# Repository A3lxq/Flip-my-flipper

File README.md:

# Flip my flipper

> **Status: UNDER DEVELOPMENT.** This is an early-stage design project. Nothing here is built, tested, certified or ready to use. Documents are drafts and will change.

A modular, portable electronics and authorised security-research handheld, designed in India to be built from parts sold by Indian sellers. The working project name is **Synnefo Handheld**. It aims to offer Flipper-Zero-style capabilities (Sub-GHz, NFC/RFID, infrared, GPIO, Wi-Fi/BLE, USB) on an independent platform with its own firmware and an open module interface standard (SMIS), with a future Linux compute module.

This project is not affiliated with, endorsed by or connected to Flipper Devices Inc. "Flipper" and "Flipper Zero" belong to their owners.

## What is here

| File | Contents |
|---|---|
| `HANDOFF.md` | **Start here when picking the project up**: status, decisions, what was verified, gaps, how to resume, next steps |
| `01-requirements-and-architecture.md` | Requirements traceability matrix, decisions (CONFIRMED / PROPOSED / OPEN), risks |
| `02-pin-maps.md` | Pin maps for STM32H743IIT6 and STM32F429ZIT6 |
| `03-core-module.md` | Swappable MCU core-module architecture and connector table |
| `04-india-sourcing.md`, `05-deep-sourcing-and-compatibility.md` | Indian sourcing and compatibility checks (snapshots, unverified stock) |
| `06-nfc-modules.md` | Two NFC modules: PN532 and ST25R3916 |
| `07-india-regulatory.md` | Indian regulatory research (not legal advice) |
| `08-smis-v0.2.md` | Synnefo Module Interface Standard v0.2 |
| `09-power-architecture.md` | Power architecture v1 |
| `10-firmware-architecture.md` | Firmware architecture v0.1 and RTOS decision record |
| `11-os-options-and-linux-architecture.md` | Other OS options and the Linux-first (Flipper One-style) question |
| `hardware/pinouts/` | Module pinout tables (with how well each pinout is known) and the connection diagrams (system and SM-S port) |
| `hardware/kicad/` | KiCad skeletons for the PN532 adapter and the ST25R3916 module, with ERC/DRC outputs |
| `firmware/board/` | Generated pin headers for both MCUs |
| `firmware/zephyr/` | Zephyr 4.5.0 toolchain setup and the three build-level de-risk test apps with results |
| `sourcing/quote-requests.md` | Drafts of quote and stock-confirmation requests to Indian sellers (not sent) |
| `research/` | Condensed research-agent reports behind the documents (limits listed in its README) |
| `CONTRIBUTING.md` | How to contribute and what the licence requires |
| `CHAT_SUMMARY.md` | Project log: decisions, findings, corrections, open items |
| `tools/` | Scripts that solve and check the pin maps |

## Ground rules

- **Lawful use only.** The device is meant for authorised testing, electronics development and education. It must not include jamming or blocking functions, and transmit features are designed to stay inside licence-exempt bands and power limits.
- **Not legal advice.** The regulatory notes list what sources say, with their gaps. They have not been reviewed by a lawyer or a test lab. Check the rules in your country before building or selling anything.
- **Stock, prices and datasheet figures are snapshots** found during research and may be wrong or out of date. Verify against the manufacturer's current datasheet and the seller before relying on anything.
- **Safety:** this design involves lithium cells and RF circuits. Do not build it without the knowledge and equipment to do so safely.

## License

GNU General Public License v3.0 or later, the same family of licence used by the Flipper Zero firmware. See [LICENSE](LICENSE), [NOTICE](NOTICE) and [CONTRIBUTING.md](CONTRIBUTING.md).

In short: anyone may use the source and build from it; if they distribute a modified version, they must publish their source under the GPL too. We ask that improvements be contributed back through pull requests, but the licence itself cannot require that.

Earlier commits (the first two) were published under Apache-2.0; anyone who copied that version keeps those rights for that version.

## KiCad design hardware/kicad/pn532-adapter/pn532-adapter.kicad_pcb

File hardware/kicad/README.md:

# KiCad skeletons for the two NFC modules

Status: **skeleton v0.1 (2026-11-02)**. Not fabricable. Nothing has been routed, ordered or built.

| Project | What it is | State |
|---|---|---|
| `pn532-adapter/` | SM-S adapter carrying the PN532 V3 breakout (Variant A, `06-nfc-modules.md` §3) | schematic + placement-only PCB (unrouted) |
| `st25r3916-module/` | ST25R3916 module (Variant B, `06-nfc-modules.md` §5) | **block-level schematic only** (blocked on ST documents and chip sourcing); no PCB |
| `lib/` | shared symbols (`synnefo.kicad_sym`) and footprints (`synnefo.pretty/`) | generic geometry, to check per chosen part |
| `tools/gen_kicad.py` | generator for all of the above (Python standard library) | reproducible: `python3 tools/gen_kicad.py hardware/kicad` |
| `checks/` | KiCad ERC, DRC and netlist outputs from this run | see below |

Open the `.kicad_pro` files with KiCad 8 or newer. The files were generated in the KiCad 8 file format and checked with `kicad-cli` 10.0.8 (official `kicad/kicad:10.0` container). Edit the generator (not the generated files) if you want the changes to survive a regeneration.

## What was checked

- **PN532 adapter schematic:** KiCad ERC reports 0 violations. The exported netlist has exactly the intended connections (`checks/pn532-adapter.nets.txt`): the SMIS SM-S port pins go to SCK, MOSI, MISO, CS (= the breakout's SSEL), IRQ; IDC and IDD go to the ID EEPROM; 3V3_P feeds the EEPROM and, through jumper JP1, the breakout; RSTPDN is pulled up.
- **PN532 adapter PCB:** KiCad DRC reports **no clearance, courtyard or board-edge violations**; the 23 "unconnected items" are the unrouted nets (expected for a placement-only board). Rendered and inspected visually.
- **ST25R3916 schematic:** KiCad ERC reports 4 errors, all intentional open items on the placeholder block: the crystal pins `XTI`, `XTO` and the antenna pin are unconnected (`checks/st25r3916-module.erc.rpt`).
- **Not checked:** electrical correctness of any value against datasheets, footprint geometry against real parts, signal integrity, EMC, or anything on the real breakout board.

## Unverified items (must be resolved before fabrication)

PN532 adapter:
1. **PN532 V3 breakout header pin order and position.** Signal names come from the Elechouse guide; the physical order, pitch and which of the board's two headers (J1 10-pin, J2 8-pin in the vendor schematic) carry which signal were not verified. Buy the board, measure it, and fix symbol `PN532_V3_Header_UNVERIFIED_ORDER`, the footprint and the placement.
2. **Breakout supply and I/O levels.** The board's regulator and the PVDD source were not found; the adapter powers it from 3V3_P through JP1 (default 1-2). Do not use 5V_P until measured (`06-nfc-modules.md` §4.2). DIP switch settings (SPI) are on the breakout, not the adapter; verify with a meter.
3. **ID EEPROM.** 24C02-class SOIC-8, address 0x50. ElectronicsComp stocks the M24C04-WMN6P (SOIC-8) and a DIP-8 24C02; the M24C04's pin 1 is not a plain A0, so check its datasheet before freezing. WP is grounded (programmable); decide the production setting.
4. **Connector.** The footprint is a generic 2x05 2.54 mm vertical header with IDC pin numbering; the real part (Probots 10-pin right-angle shrouded box header was found in stock), its orientation, outline and mating cable are not chosen.
5. **Passives.** 0603 pad geometry is approximate; the 10 uF value and voltage rating are not selected; IRQ pull-up, if any, belongs on the carrier (SMIS) and is not on the adapter.
6. **Routing, mounting holes, board shape, silkscreen.** Not done.

ST25R3916 module:
1. Pin numbers marked `TBD-n` are unknown; only pins 1, 3, 7, 8, 9, 10, 11, 14 and 33 come from DS12484 Rev 3 text (an old revision).
2. The decoupling capacitor net assignments, the VDD_RF/VDD_DR tie and the supply plan are placeholders to confirm against DS12484/DS13541 Figure 1 and §4.2.11.
3. Absent on purpose: antenna coil, EMC filter, matching network, 27.12 MHz crystal and load capacitors, exposed-pad thermal vias, layout. They need AN5276, AN5240, AN5322, AN5592 and the NFC08A1 design files (`06-nfc-modules.md` §9).
4. No Indian source for the chip was found (`04-` to `06-`).

## Parts list (draft, nothing ordered; Indian-stock status from `04-`, `05-`, `06-`)

PN532 adapter:

| Ref | Part | Source and status |
|---|---|---|
| (module) | PN532 V3 breakout | DNA Tech India, ₹317.43 incl. GST, stock 50 (page opened 2026-11-01) |
| J1 | 2x05 2.54 mm shrouded box header | Probots, ₹17 incl. GST, in stock (right-angle); orientation/footprint to confirm |
| JP1, J2 | 1x03 and 1x08 2.54 mm pin headers, shunt | generic; not yet searched |
| U1 | 24C02-class EEPROM, SOIC-8 | ElectronicsComp M24C04-WMN6P ₹17 ex GST (154 in stock); check pin-1 difference |
| C1 | 100 nF 0603 | generic stocked family (Evelta, Probots listings); part not chosen |
| C2 | 10 uF 0603, rating TBD | Probots has a Samsung 22 uF 0805; 0603 10 uF not chosen |
| R1 | 10 kohm 0603 | generic stocked family |

ST25R3916 module: chip, crystal, antenna parts all TBD (see unverified list); ID EEPROM and decoupling as for the adapter.

## Reproduce the checks

```bash
cd hardware/kicad
k() { docker run --rm --user "$(id -u):$(id -g)" -e HOME=/tmp -v "$PWD:/work" -w /work kicad/kicad:10.0 kicad-cli "$@"; }
k sch erc --severity-all --format report -o /work/checks/pn532-adapter.erc.rpt pn532-adapter/pn532-adapter.kicad_sch
k pcb drc --severity-all --format report -o /work/checks/pn532-adapter.drc.rpt pn532-adapter/pn532-adapter.kicad_pcb
```

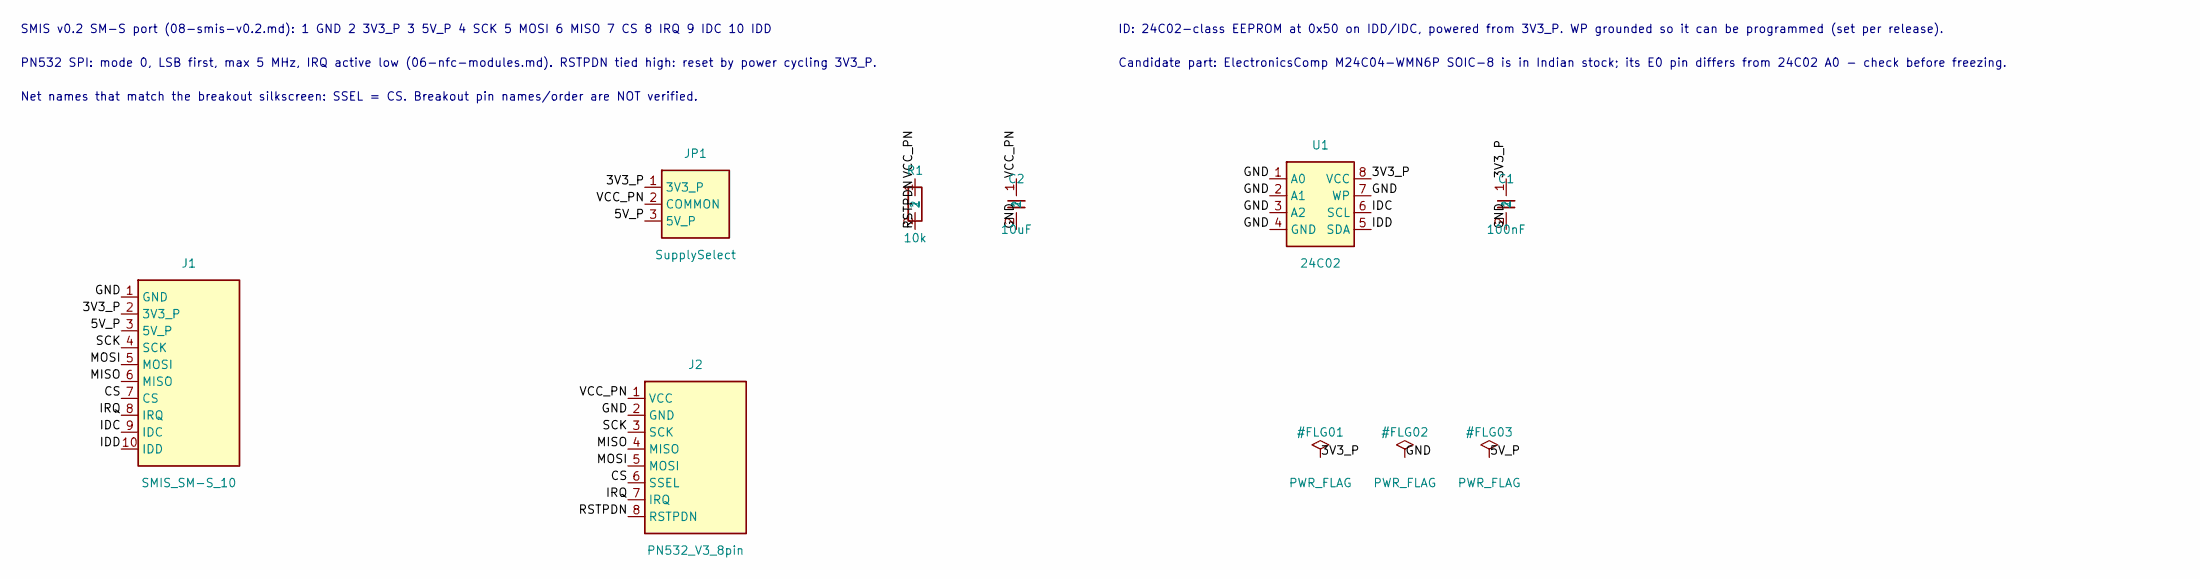
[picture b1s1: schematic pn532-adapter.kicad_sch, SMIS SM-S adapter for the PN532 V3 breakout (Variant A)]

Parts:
C1: 100nF; C_0603_1608Metric
C2: 10uF; C_0603_1608Metric
J1: SMIS_SM-S_10; IDC_Header_2x05_P2.54mm_Vertical
J2: PN532_V3_8pin; PinHeader_1x08_P2.54mm_Vertical
JP1: SupplySelect; PinHeader_1x03_P2.54mm_Vertical
R1: 10k; R_0603_1608Metric
U1: 24C02; SOIC-8_3.9x4.9mm_P1.27mm

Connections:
3V3_P: C1.1, J1.2 (3V3_P), JP1.1 (3V3_P), U1.8 (VCC)
5V_P: J1.3 (5V_P), JP1.3 (5V_P)
CS: J1.7 (CS), J2.6 (SSEL)
GND: C1.2, C2.2, J1.1 (GND), J2.2 (GND), U1.1 (A0), U1.2 (A1), U1.3 (A2), U1.4 (GND), U1.7 (WP)
IDC: J1.9 (IDC), U1.6 (SCL)
IDD: J1.10 (IDD), U1.5 (SDA)
IRQ: J1.8 (IRQ), J2.7 (IRQ)
MISO: J1.6 (MISO), J2.4 (MISO)
MOSI: J1.5 (MOSI), J2.5 (MOSI)
RSTPDN: J2.8 (RSTPDN), R1.2
SCK: J1.4 (SCK), J2.3 (SCK)
VCC_PN: C2.1, J2.1 (VCC), JP1.2 (COMMON), R1.1

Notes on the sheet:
SMIS v0.2 SM-S port (08-smis-v0.2.md): 1 GND 2 3V3_P 3 5V_P 4 SCK 5 MOSI 6 MISO 7 CS 8 IRQ 9 IDC 10 IDD
PN532 SPI: mode 0, LSB first, max 5 MHz, IRQ active low (06-nfc-modules.md). RSTPDN tied high: reset by power cycling 3V3_P.
Net names that match the breakout silkscreen: SSEL = CS. Breakout pin names/order are NOT verified.
ID: 24C02-class EEPROM at 0x50 on IDD/IDC, powered from 3V3_P. WP grounded so it can be programmed (set per release).
Candidate part: ElectronicsComp M24C04-WMN6P SOIC-8 is in Indian stock; its E0 pin differs from 24C02 A0 - check before freezing.

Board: 2 copper layers, 7 parts (0 on the bottom side), 12 nets, no tracks yet.

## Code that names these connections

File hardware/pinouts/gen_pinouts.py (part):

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

def port_pins(chip_map, n):
    s = f"IDD {pin(chip_map, f'IDD_P{n}')} IDC {pin(chip_map, f'IDC_P{n}')} IRQ {pin(chip_map, f'IRQ_P{n}')}"
    if n <= 5:
        s += f" CS {pin(chip_map, f'CS_P{n}')}"
    return s
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}
MOD_NOTE = {
    "CC1101 module (chip pins)": "GDO2 (pin 3 [P]) has no contact; vendor breakout headers differ (8 and 10 pin boards)",
    "PN532 V3 breakout (signals)": "header ORDER unverified [V]; RSTPDN pulled up on the adapter; chip pins [P]: NSS 27, MOSI 28, MISO 29, SCK 30, IRQ 25, RSTPD_N 38",
    "ST25R3916 module (chip pins)": "I2C_EN tied to GND; no reset pin; other pin numbers unknown until DS12484 Table 2 is read",
}

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    ax.set_ylim(0, 17)
    ax.axis("off")
    ax.text(12, 16.65, "SM-S port: contact-by-contact connection of the SPI modules (port P1 shown)", ha="center", fontsize=15, fontweight="bold")
    ax.text(12, 16.3, "Left: MCU pins (F429 | H743). Centre: SMIS v0.2 contacts (2x5 header, IDC numbering). Right: module pins. "
            "Tags: [P] datasheet read, [V] vendor guide, [K] my recollection, unverified, ? unknown.", ha="center", fontsize=9, color="#444")
    row_h = 0.62
    top = 15.2
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    py = 6.9
    ax.text(0.4, py, "SM-U port (P8, UART) with RDM6300 125 kHz reader", fontsize=11.5, fontweight="bold")
    ax.text(0.4, py - 0.35, "contacts 4-8 change meaning per class; 1, 2, 3, 9, 10 never change", fontsize=8.6, color="#444")
    SMU = ["GND", "3V3_P", "5V_P", "TX (module out)", "RX (module in)", "IRQ", "GPIO", "n/c", "IDC", "IDD"]
    SMU_MCU = {"TX (module out)": "UART_EXP_RX", "RX (module in)": "UART_EXP_TX", "IRQ": "IRQ_P8", "IDC": "IDC_P8", "IDD": "IDD_P8"}
    RDM = ["GND", "(not used)", "5V supply", "TX (UART out, level unverified) [V]", "(RX, if present) ?", "-", "-", "-", "ID EEPROM SCL", "ID EEPROM SDA"]
    rh = 0.4
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    # SM-I panel
    ax.text(14.2, py, "SM-I port (P6, P7, I2C): generic sensor/module", fontsize=11.5, fontweight="bold")
    ax.text(14.2, py - 0.35, "I2C bus is shared by both SM-I ports (I2C2)", fontsize=8.6, color="#444")
    SMI = ["GND", "3V3_P", "5V_P", "SDA", "SCL", "IRQ", "GPIO (opt)", "n/c", "IDC", "IDD"]
    SMI_MCU = {"SDA": "I2C_EXP_SDA", "SCL": "I2C_EXP_SCL", "IRQ": "IRQ_P6", "IDC": "IDC_P6", "IDD": "IDD_P6"}
    for i, net in enumerate(SMI):
        y = top2 - rh * i
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

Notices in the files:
hardware/pinouts/gen_pinouts.py:
SPDX-License-Identifier: GPL-3.0-or-later
